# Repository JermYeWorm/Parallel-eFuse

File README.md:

# Parallel eFuse Development Board
Parallel eFuse Dev Board for Robotics @ Maryland. Paralleled TPS25982 15A eFuse protection board designed to protect against current transients of up to 30A from RoboSub's electronic speed controllers. Built with KiCad 7.0.
<br><br>

## Design Visuals

<br>_Fig 1. Schematic Capture_<br><br>

<br>_Fig 2. 2D PCB Layout_<br><br>

<br>_Fig 3. 3D Model (no components)_<br><br>

<br>_Fig 4. 3D Model (mounted components)_<br><br>

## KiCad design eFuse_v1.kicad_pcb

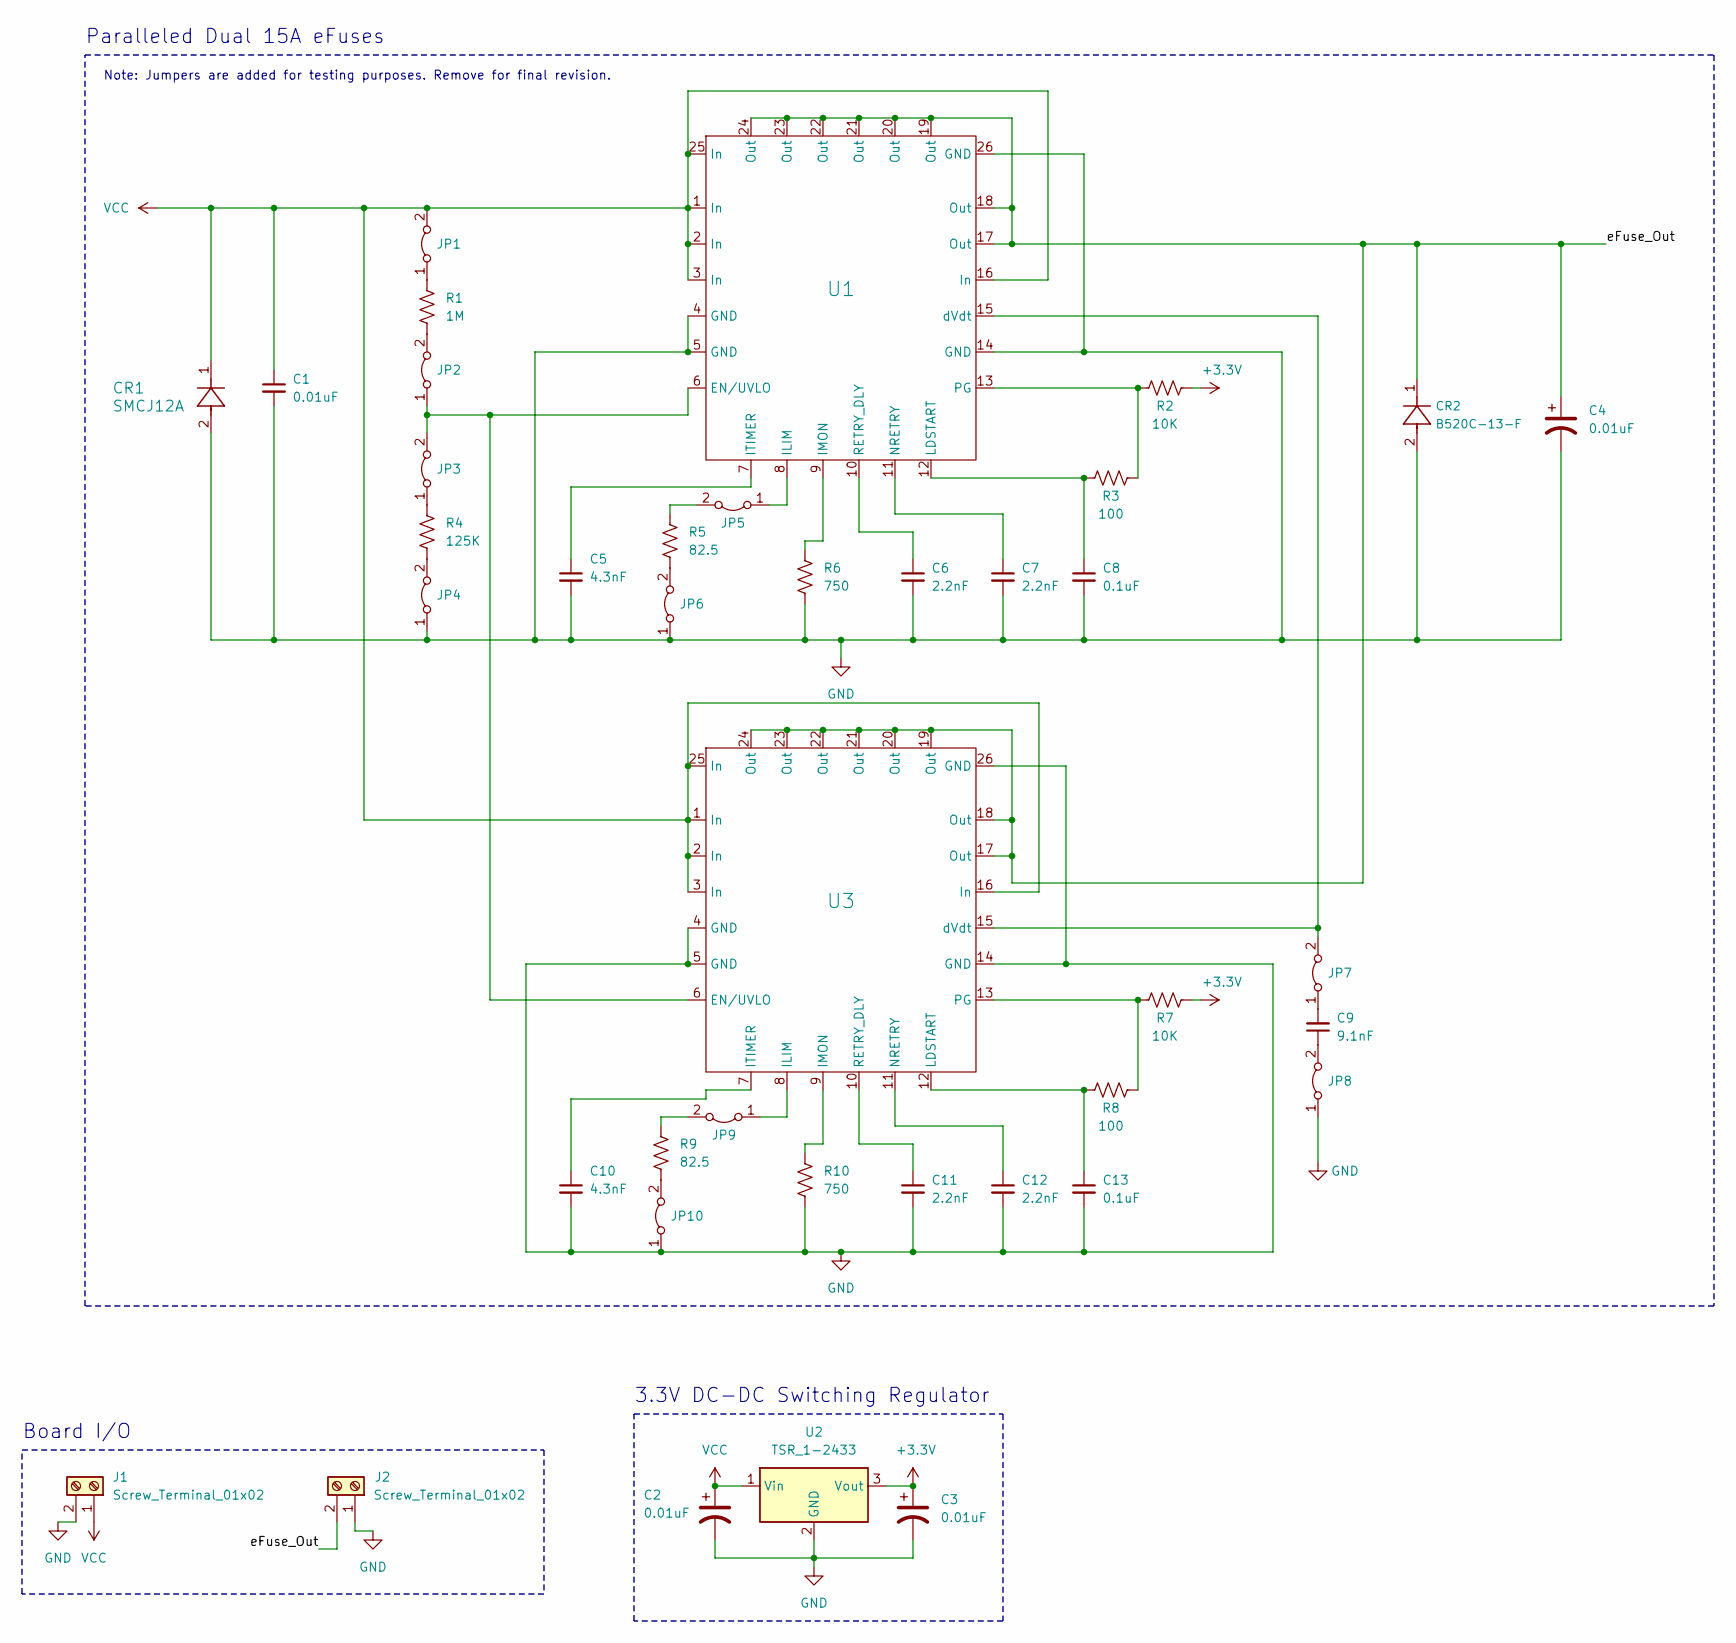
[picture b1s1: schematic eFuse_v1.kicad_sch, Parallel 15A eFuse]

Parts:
C1, C2, C3, C4: 0.01uF; CAP_GRM033_MUR
C5, C10: 4.3nF; CAPC340180_100N_KEM
C6, C7, C11, C12: 2.2nF; CAPC10555_55N_KEM
C8, C13: 0.1uF; CAPC0603X33N
C9: 9.1nF; CAPC2012X95N
CR1: SMCJ12A; D_SMC
CR2: B520C-13-F; D_SMC
J1, J2: Screw_Terminal_01x02; TerminalBlock_Phoenix_PT-1,5-2-5.0-H_1x02_P5.00mm_Horizontal
JP1, JP2, JP3, JP4, JP5, JP6, JP7, JP8, JP9, JP10: Jumper_2_Bridged; PinHeader_1x02_P2.54mm_Vertical
R1: 1M; RES_ERJ2RKF1004X
R2, R7: 10K; BO_CR0402
R3, R8: 100; RC0402N_YAG
R4: 125K; RESC1005X35N
R5, R9: 82.5; YAG_R0402_YAG
R6, R10: 750; RESC1005X40N
U1, U3: RGE24_2P5XP85X1P45_TEX
U2: TSR_1-2433; Converter_DCDC_TRACO_TSR-1_THT

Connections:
+3.3V: C3.1, R2.2, R7.2, U2.3 (Vout)
/eFuse_Out: C4.1, CR2.1, J2.2, U1.17 (Out), U1.18 (Out), U1.19 (Out), U1.20 (Out), U1.21 (Out), U1.22 (Out), U1.23 (Out), U1.24 (Out), U3.17 (Out), U3.18 (Out), U3.19 (Out), U3.20 (Out), U3.21 (Out), U3.22 (Out), U3.23 (Out), U3.24 (Out)
GND: C1.2, C2.2, C3.2, C4.2, C5.2, C6.2, C7.2, C8.2, C10.2, C11.2, C12.2, C13.2, CR1.2, CR2.2, J1.2, J2.1, JP4.1 (A), JP6.1 (A), JP8.1 (A), JP10.1 (A), R6.2, R10.2, U1.4 (GND), U1.5 (GND), U1.14 (GND), U1.26 (GND), U2.2 (GND), U3.4 (GND), U3.5 (GND), U3.14 (GND), U3.26 (GND)
unnamed: JP1.1 (A), R1.1
unnamed: JP2.1 (A), JP3.2 (B), U1.6 (EN/UVLO), U3.6 (EN/UVLO)
unnamed: JP2.2 (B), R1.2
unnamed: JP3.1 (A), R4.1
unnamed: JP4.2 (B), R4.2
unnamed: JP5.1 (A), U1.8 (ILIM)
unnamed: JP5.2 (B), R5.1
unnamed: JP6.2 (B), R5.2
unnamed: C9.2, JP7.1 (A)
unnamed: JP7.2 (B), U1.15 (dVdt), U3.15 (dVdt)
unnamed: C9.1, JP8.2 (B)
unnamed: JP9.1 (A), U3.8 (ILIM)
unnamed: JP9.2 (B), R9.1
unnamed: JP10.2 (B), R9.2
unnamed: R6.1, U1.9 (IMON)
unnamed: C5.1, U1.7 (ITIMER)
unnamed: C8.1, R3.1, U1.12 (LDSTART)
unnamed: C7.1, U1.11 (NRETRY)
unnamed: R2.1, R3.2, U1.13 (PG)
unnamed: C6.1, U1.10 (RETRY_DLY)
unnamed: R10.1, U3.9 (IMON)
unnamed: C10.1, U3.7 (ITIMER)
unnamed: C13.1, R8.1, U3.12 (LDSTART)
unnamed: C12.1, U3.11 (NRETRY)
unnamed: R7.1, R8.2, U3.13 (PG)
unnamed: C11.1, U3.10 (RETRY_DLY)
VCC: C1.1, C2.1, CR1.1, J1.1, JP1.2 (B), U1.1 (In), U1.2 (In), U1.3 (In), U1.16 (In), U1.25 (In), U2.1 (Vin), U3.1 (In), U3.2 (In), U3.3 (In), U3.16 (In), U3.25 (In)

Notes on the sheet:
3.3V DC-DC Switching Regulator
Note: Jumpers are added for testing purposes. Remove for final revision.
Board I/O
Paralleled Dual 15A eFuses

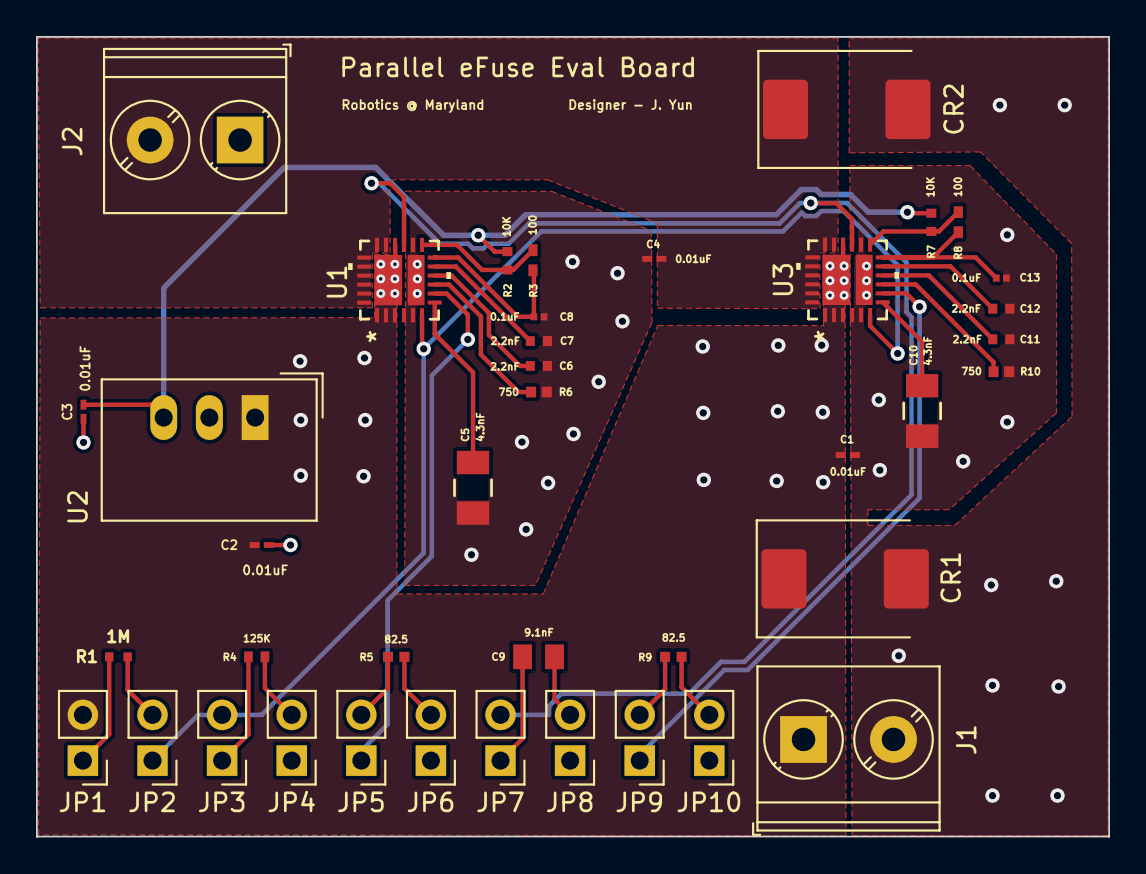
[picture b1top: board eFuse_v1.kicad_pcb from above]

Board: 2 copper layers, 59.6 x 44.4 mm, 40 parts (0 on the bottom side), 30 nets.

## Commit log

2024-02-24 3d model update
2024-02-24 updated 3d models
